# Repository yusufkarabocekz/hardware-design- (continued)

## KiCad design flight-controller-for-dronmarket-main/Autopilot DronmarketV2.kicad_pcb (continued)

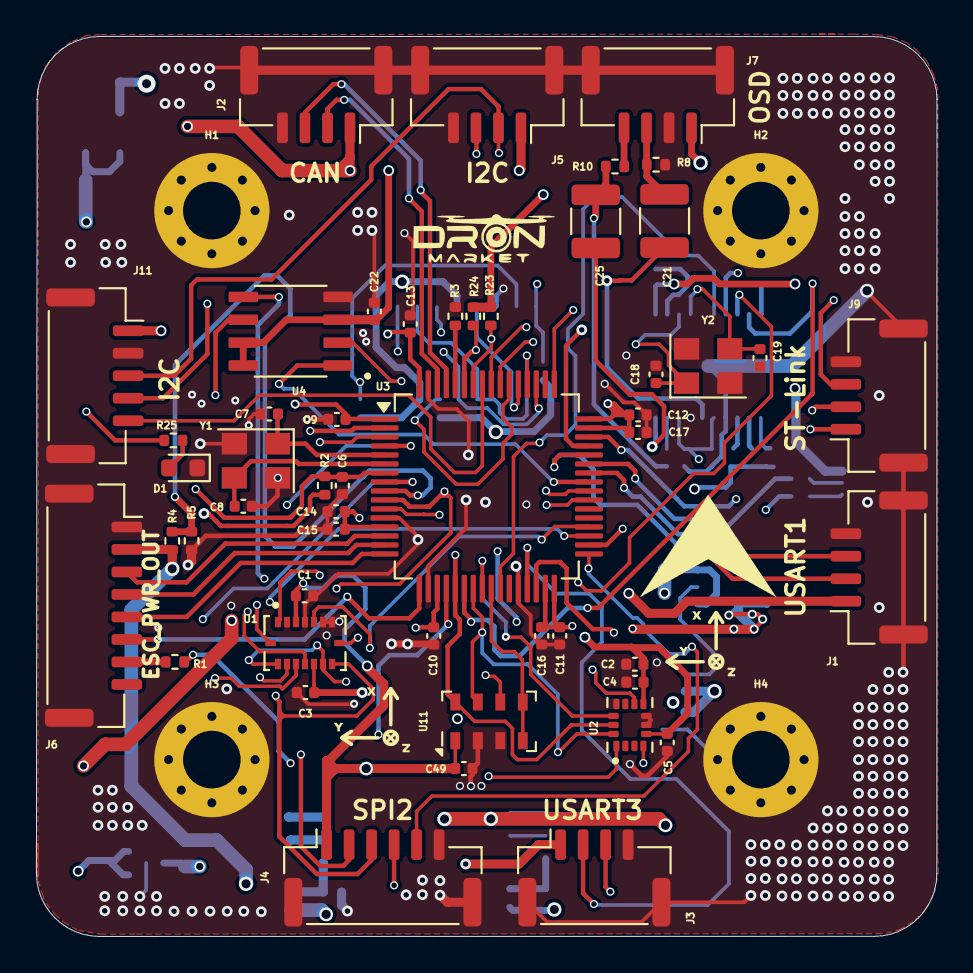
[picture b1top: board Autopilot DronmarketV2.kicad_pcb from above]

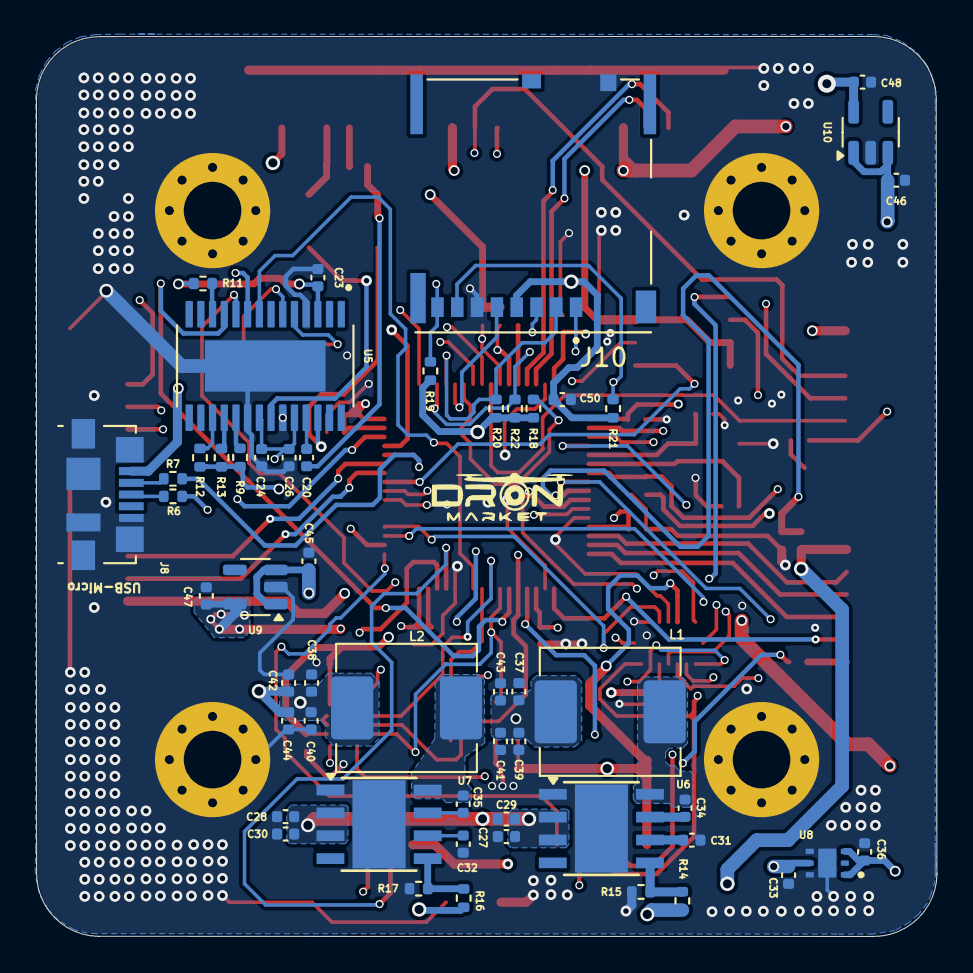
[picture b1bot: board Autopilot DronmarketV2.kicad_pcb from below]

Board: 6 copper layers, 50.0 x 50.0 mm, 111 parts (53 on the bottom side), 79 nets.

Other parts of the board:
., .#2, .#3, .#4, .#5: LOGO
C37, C39: 22uF; C_0402_1005Metric

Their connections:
GND: C37.1, C39.1; also elsewhere on the board
VDD_5V_IN: C37.2, C39.2; also elsewhere on the board

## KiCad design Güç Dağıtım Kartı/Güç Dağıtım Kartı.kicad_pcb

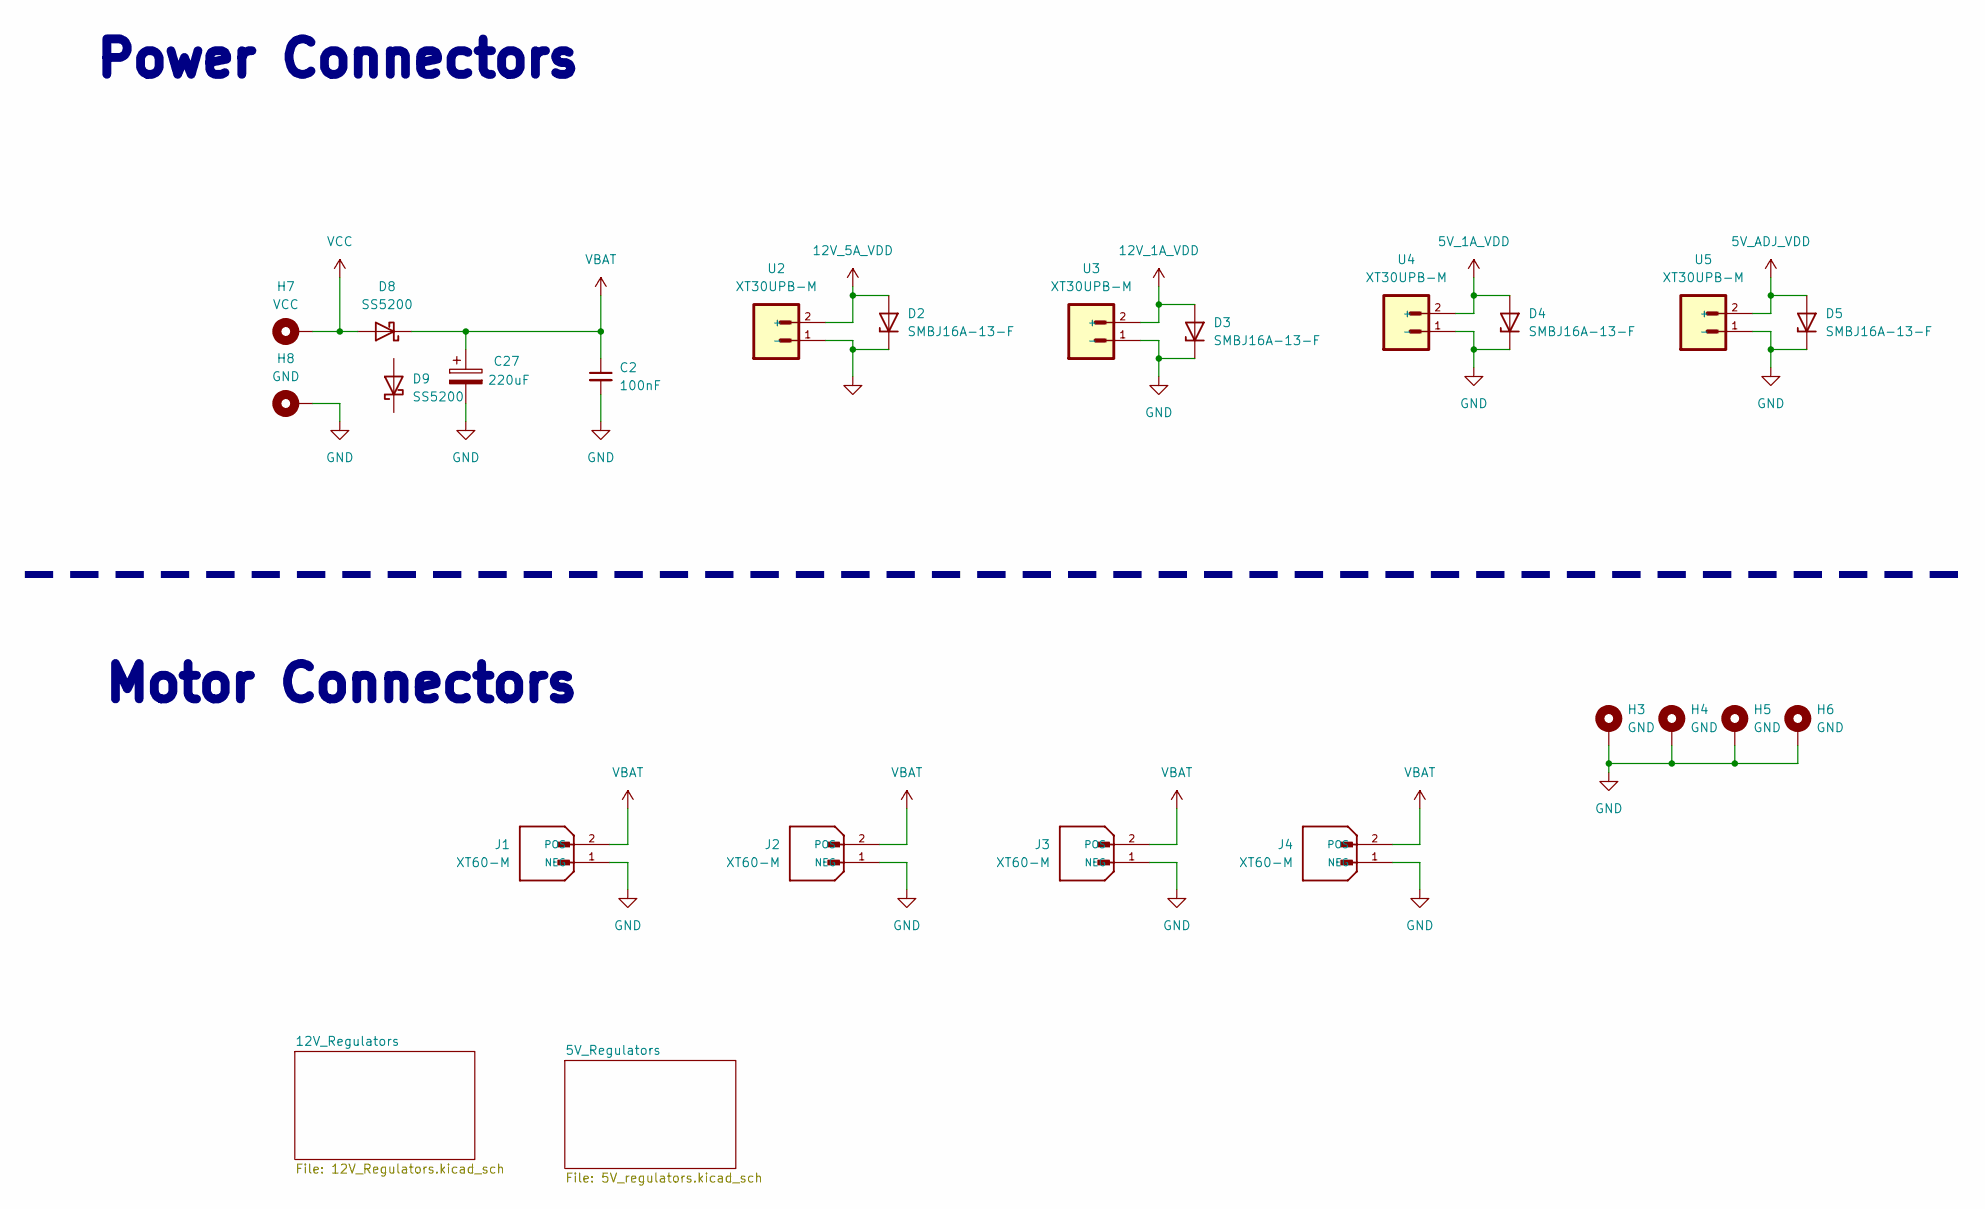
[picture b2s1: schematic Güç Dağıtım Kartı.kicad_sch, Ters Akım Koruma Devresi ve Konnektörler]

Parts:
C2: 100nF; C_1206_3216Metric
C27: 220uF; CP_EIA-7343-43_Kemet-X_HandSolder
D2, D3, D4, D5: SMBJ16A-13-F; D_SMA
D8, D9: SS5200; D_SMA
H3, H4, H5, H6: GND; MountingHole_3.2mm_M3_ISO14580
H7: VCC; MountingHole_4.3mm_M4_Pad_TopOnly
H8: GND; MountingHole_4.3mm_M4_Pad_TopOnly
J1, J2, J3, J4: XT60-M; AMASS_XT60-F_1x02_P7.20mm_Vertical; PARTREV V1.2
U2, U3, U4, U5: XT30UPB-M; AMASS_XT30UPB-M_1x02_P5.0mm_Vertical

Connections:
5V_1A_VDD: D4.2 (A), U4.2 (+); also elsewhere on the board
5V_ADJ_VDD: D5.2 (A), U5.2 (+); also elsewhere on the board
12V_1A_VDD: D3.2 (A), U3.2 (+); also elsewhere on the board
12V_5A_VDD: D2.2 (A), U2.2 (+); also elsewhere on the board
GND: C2.2, C27.2, D2.1 (K), D3.1 (K), D4.1 (K), D5.1 (K), H3.MP, H4.MP, H5.MP, H6.MP, H8.1, J1.1 (NEG), J2.1 (NEG), J3.1 (NEG), J4.1 (NEG), U2.1 (-), U3.1 (-), U4.1 (-), U5.1 (-); also elsewhere on the board
VBAT: C2.1, C27.1, D8.1 (K), J1.2 (POS), J2.2 (POS), J3.2 (POS), J4.2 (POS); also elsewhere on the board
VCC: D8.2 (A), H7.1

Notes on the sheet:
Power Connectors
Motor Connectors

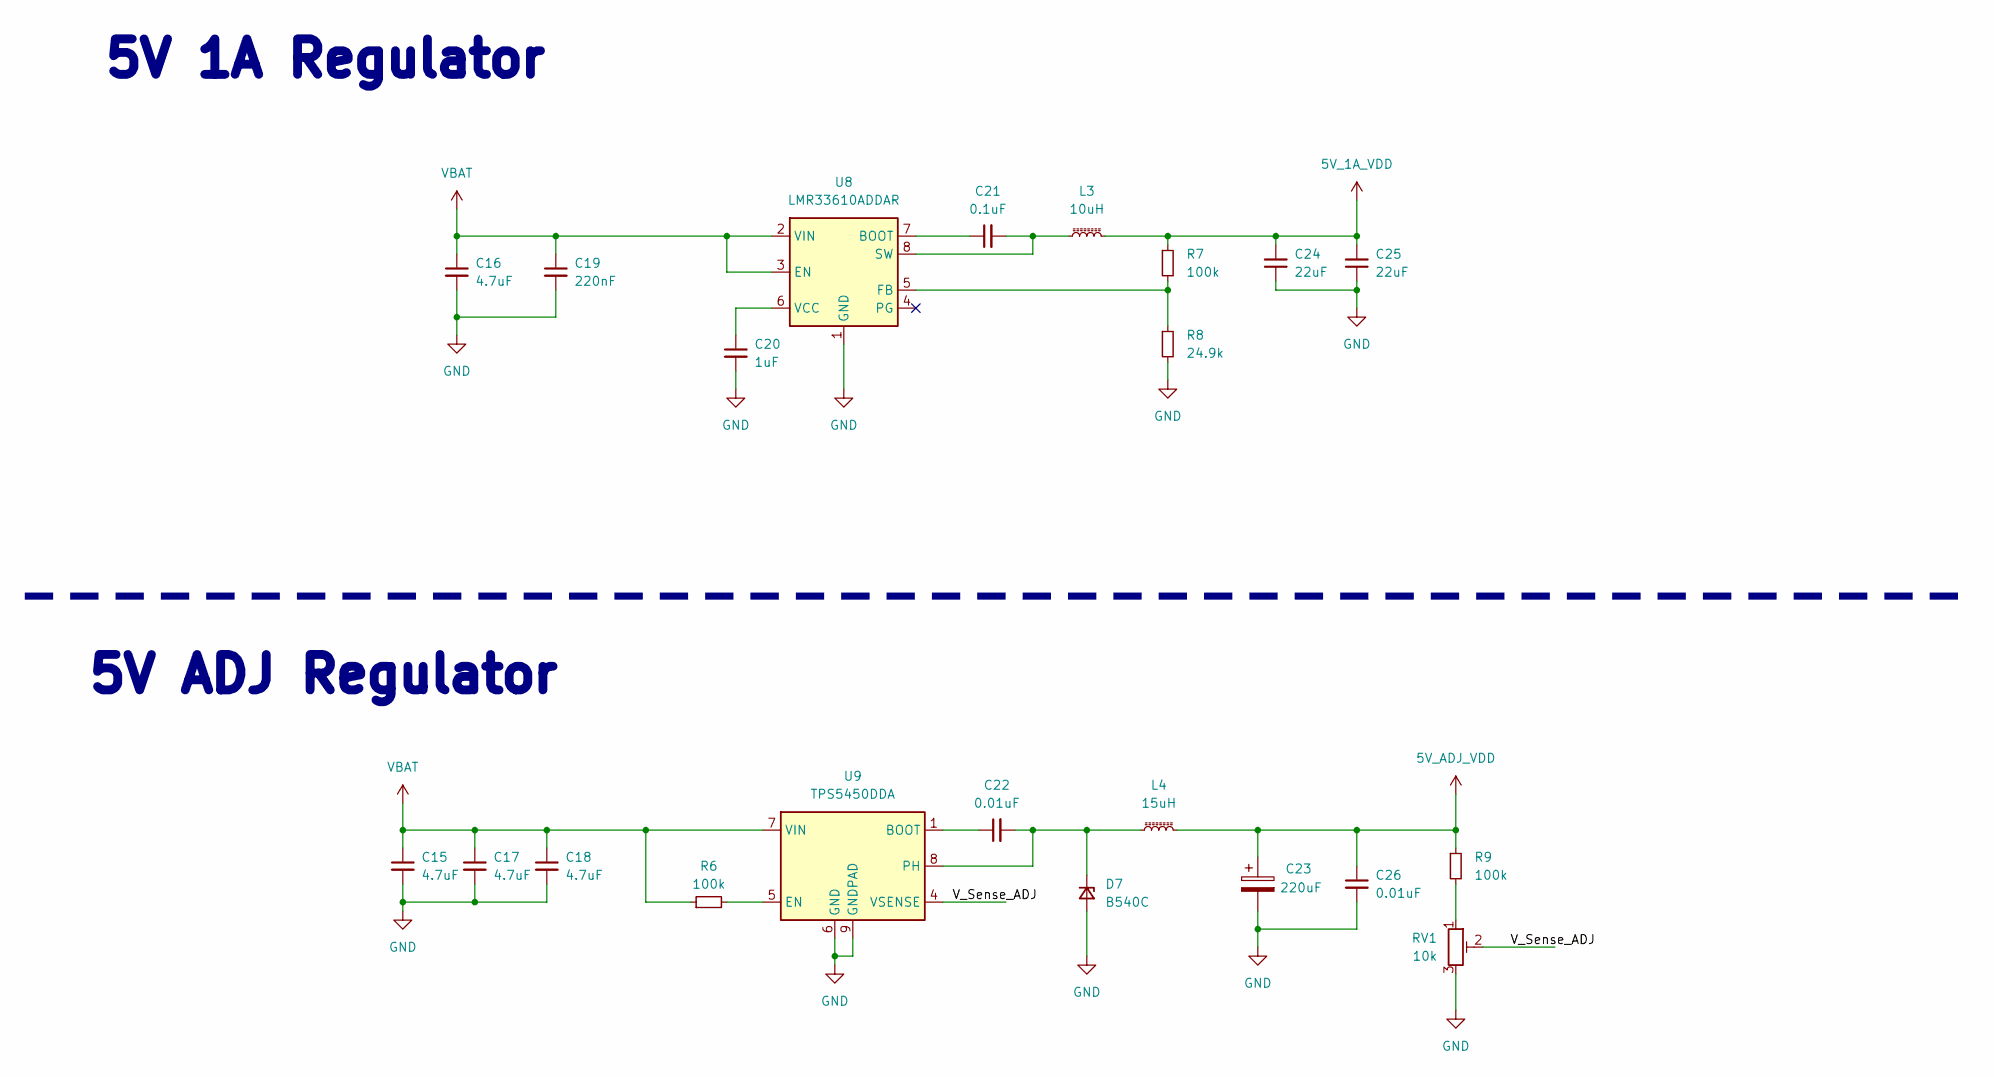
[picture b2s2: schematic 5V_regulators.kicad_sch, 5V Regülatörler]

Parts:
C15, C17, C18: 4.7uF; C_0603_1608Metric_Pad1.08x0.95mm_HandSolder
C16: 4.7uF; C_1206_3216Metric_Pad1.33x1.80mm_HandSolder
C19: 220nF; C_0603_1608Metric_Pad1.08x0.95mm_HandSolder
C20: 1uF; C_0603_1608Metric_Pad1.08x0.95mm_HandSolder
C21: 0.1uF; C_0603_1608Metric_Pad1.08x0.95mm_HandSolder
C22, C26: 0.01uF; C_0603_1608Metric_Pad1.08x0.95mm_HandSolder
C23: 220uF; CP_EIA-7343-43_Kemet-X_HandSolder
C24, C25: 22uF; C_1206_3216Metric_Pad1.33x1.80mm_HandSolder
D7: B540C; D_SMA
L3: 10uH; L_7.3x7.3_H3.5
L4: 15uH; L_7.3x7.3_H3.5
R6, R7, R9: 100k; R_0603_1608Metric_Pad0.98x0.95mm_HandSolder
R8: 24.9k; R_0603_1608Metric_Pad0.98x0.95mm_HandSolder
RV1: 10k; Potentiometer_Bourns_3296W_Vertical
U8: LMR33610ADDAR; Texas_HSOP-8-1EP_3.9x4.9mm_P1.27mm_ThermalVias
U9: TPS5450DDA; TI_SO-PowerPAD-8_ThermalVias

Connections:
5V_1A_VDD: C24.2, C25.2, L3.2, R7.1; also elsewhere on the board
5V_ADJ_VDD: C23.1, C26.1, L4.2, R9.1; also elsewhere on the board
/5V_Regulators/V_Sense_ADJ: RV1.2, U9.4 (VSENSE)
GND: C15.2, C16.2, C17.2, C18.2, C19.2, C20.2, C23.2, C24.1, C25.1, C26.2, D7.2 (A), R8.2, RV1.3, U8.1 (GND), U8.9 (GND), U9.6 (GND), U9.9 (GNDPAD); also elsewhere on the board
unnamed: C22.2, D7.1 (K), L4.1, U9.8 (PH)
unnamed: R9.2, RV1.1
unnamed: C21.1, U8.7 (BOOT)
unnamed: R7.2, R8.1, U8.5 (FB)
unnamed: C21.2, L3.1, U8.8 (SW)
unnamed: C20.1, U8.6 (VCC)
unnamed: C22.1, U9.1 (BOOT)
unnamed: R6.2, U9.5 (EN)
VBAT: C15.1, C16.1, C17.1, C18.1, C19.1, R6.1, U8.2 (VIN), U8.3 (EN), U9.7 (VIN); also elsewhere on the board

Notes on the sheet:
5V ADJ Regulator
5V 1A Regulator

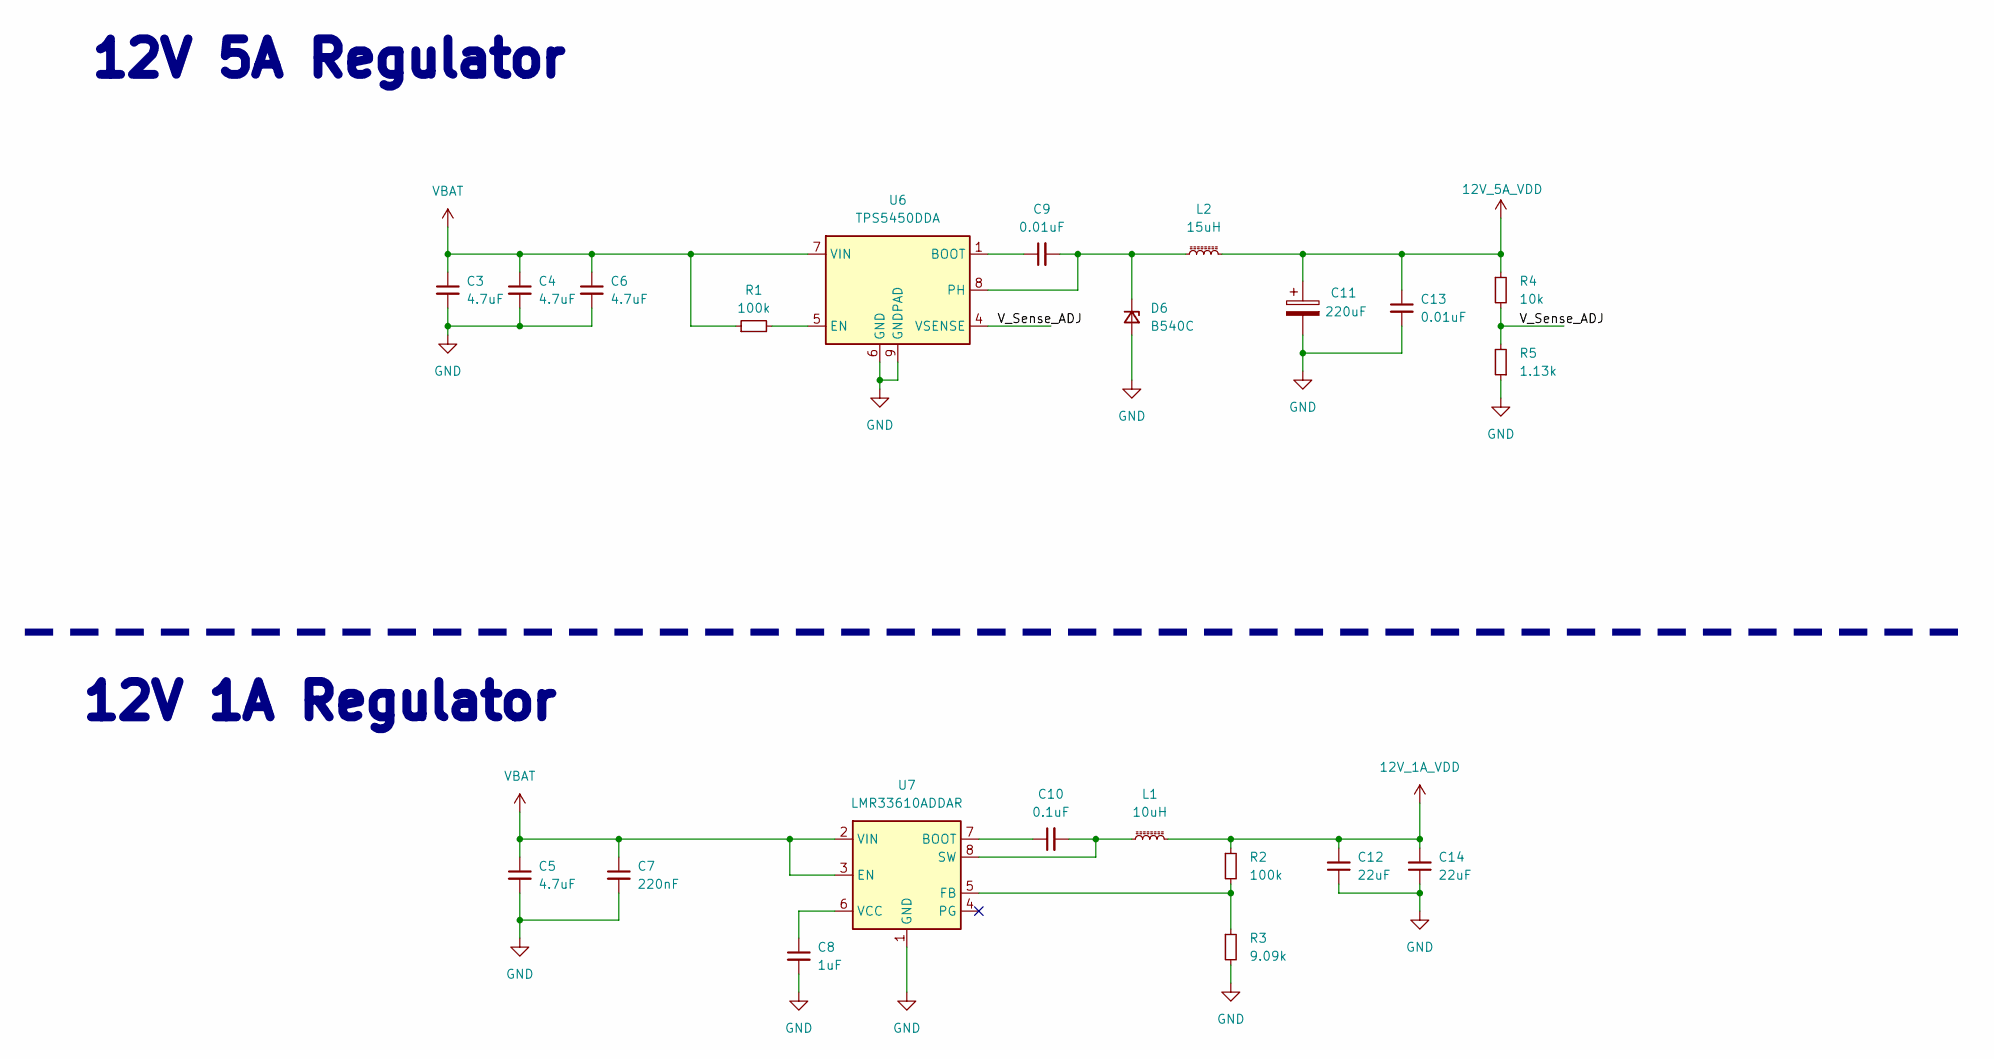
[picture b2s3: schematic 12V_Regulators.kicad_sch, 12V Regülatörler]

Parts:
C3, C4, C6: 4.7uF; C_0603_1608Metric_Pad1.08x0.95mm_HandSolder
C5: 4.7uF; C_1206_3216Metric_Pad1.33x1.80mm_HandSolder
C7: 220nF; C_0603_1608Metric_Pad1.08x0.95mm_HandSolder
C8: 1uF; C_0603_1608Metric_Pad1.08x0.95mm_HandSolder
C9, C13: 0.01uF; C_0603_1608Metric_Pad1.08x0.95mm_HandSolder
C10: 0.1uF; C_0603_1608Metric_Pad1.08x0.95mm_HandSolder
C11: 220uF; CP_EIA-7343-43_Kemet-X_HandSolder
C12, C14: 22uF; C_1206_3216Metric_Pad1.33x1.80mm_HandSolder
D6: B540C; D_SMA
L1: 10uH; L_7.3x7.3_H3.5
L2: 15uH; L_7.3x7.3_H3.5
R1, R2: 100k; R_0603_1608Metric_Pad0.98x0.95mm_HandSolder
R3: 9.09k; R_0603_1608Metric_Pad0.98x0.95mm_HandSolder
R4: 10k; R_0603_1608Metric_Pad0.98x0.95mm_HandSolder
R5: 1.13k; R_0603_1608Metric_Pad0.98x0.95mm_HandSolder
U6: TPS5450DDA; TI_SO-PowerPAD-8_ThermalVias
U7: LMR33610ADDAR; Texas_HSOP-8-1EP_3.9x4.9mm_P1.27mm_ThermalVias

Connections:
12V_1A_VDD: C12.2, C14.2, L1.2, R2.1; also elsewhere on the board
12V_5A_VDD: C11.1, C13.1, L2.2, R4.1; also elsewhere on the board
/12V_Regulators/V_Sense_ADJ: R4.2, R5.2, U6.4 (VSENSE)
GND: C3.2, C4.2, C5.2, C6.2, C7.2, C8.2, C11.2, C12.1, C13.2, C14.1, D6.2 (A), R3.2, R5.1, U6.6 (GND), U6.9 (GNDPAD), U7.1 (GND), U7.9 (GND); also elsewhere on the board
unnamed: C9.2, D6.1 (K), L2.1, U6.8 (PH)
unnamed: C9.1, U6.1 (BOOT)
unnamed: R1.2, U6.5 (EN)
unnamed: C10.1, U7.7 (BOOT)
unnamed: R2.2, R3.1, U7.5 (FB)
unnamed: C10.2, L1.1, U7.8 (SW)
unnamed: C8.1, U7.6 (VCC)
VBAT: C3.1, C4.1, C5.1, C6.1, C7.1, R1.1, U6.7 (VIN), U7.2 (VIN), U7.3 (EN); also elsewhere on the board

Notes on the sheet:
12V 5A Regulator
12V 1A Regulator

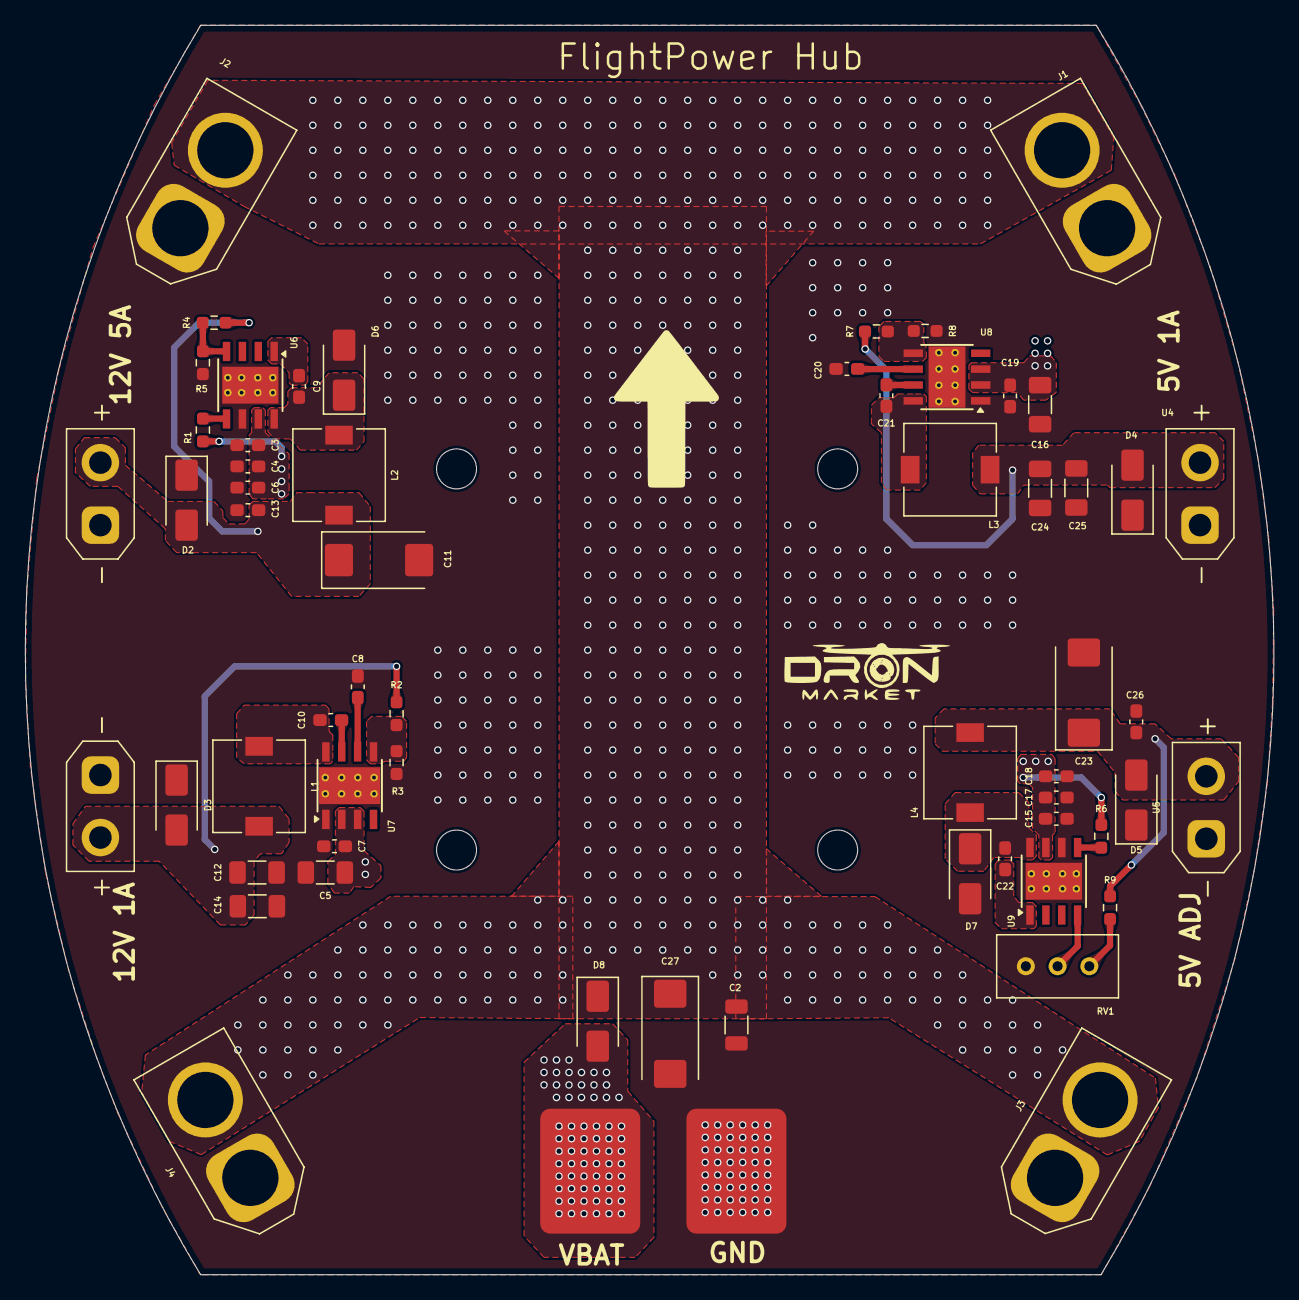
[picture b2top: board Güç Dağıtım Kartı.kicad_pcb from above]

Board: 4 copper layers, 99.9 x 100.0 mm, 65 parts (0 on the bottom side), 24 nets.

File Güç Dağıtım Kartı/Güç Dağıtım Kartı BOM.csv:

Id;Designator;Footprint;Quantity;Designation;Supplier and ref
1;J3,M1,J1,J4;AMASS_XT60-F_1x02_P7.20mm_Vertical;4;XT60-M;
2;,,,,,,,,,,,,,,,,,,,,,,,,,,,,,,,,,,,,;;37;;
3;R2,R7,R6,R9,R1;R_0603_1608Metric;5;100k;
4;D6,D7;D_SMA;2;B540C;
5;C26,C22,C9,C13;C_0603_1608Metric_Pad1.08x0.95mm_HandSolder;4;0.01uF;
6;12V_5A Jetson Nano,12V_1A;AMASS_XT30UPB-M_1x02_P5.0mm_Vertical;2;XT30UPB-M;
7;R4;R_0603_1608Metric;1;10k;
8;C8,C20;C_0603_1608Metric_Pad1.08x0.95mm_HandSolder;2;1uF;
9;C16,C5;C_1206_3216Metric;2;4.7uF;
10;C19,C7;C_0603_1608Metric_Pad1.08x0.95mm_HandSolder;2;220nF;
11;RV1;Potentiometer_Bourns_3266Z_Horizontal;1;10k;
12;C3,C6,C18,C4,C15,C17;C_0603_1608Metric_Pad1.08x0.95mm_HandSolder;6;4.7uF;
13;R5;R_0603_1608Metric;1;1.13k;
14;R8;R_0603_1608Metric;1;24.9k;
15;L4,L2;L_Wurth_WE-LQSH-4020;2;15uH;
16;U6,U9;TI_SO-PowerPAD-8_ThermalVias;2;TPS5450DDA;
17;D4,D2,D5,D3;D_SMA;4;D_Zener;
18;5V_1A,5V_ADJ;AMASS_XT30U-F_1x02_P5.0mm_Vertical;2;XT30UPB-M;
19;C12,C14,C25,C24;C_1206_3216Metric;4;22uF;
20;U8,U7;Texas_HSOP-8-1EP_3.9x4.9mm_P1.27mm_ThermalVias;2;LMR33610ADDAR;
21;C11,C23;CP_EIA-1608-10_AVX-L;2;330uF;
22;;29548ad2-03e3-42cf-bff7-278db09b4abb;1;;
23;D1;D_SMA_Handsoldering;1;SB130;
24;L3,L1;L_Wurth_WE-LQSH-4020;2;10uH;
25;C1;CP_EIA-7343-40_Kemet-Y;1;C_Polarized;
26;C2;C_1206_3216Metric;1;100nF;
27;R3;R_0603_1608Metric;1;9.09k;
28;C21,C10;C_0603_1608Metric_Pad1.08x0.95mm_HandSolder;2;0.1uF;
29;;2d8a1ed6-01ba-462d-b9ff-4f236c5c597e;1;;

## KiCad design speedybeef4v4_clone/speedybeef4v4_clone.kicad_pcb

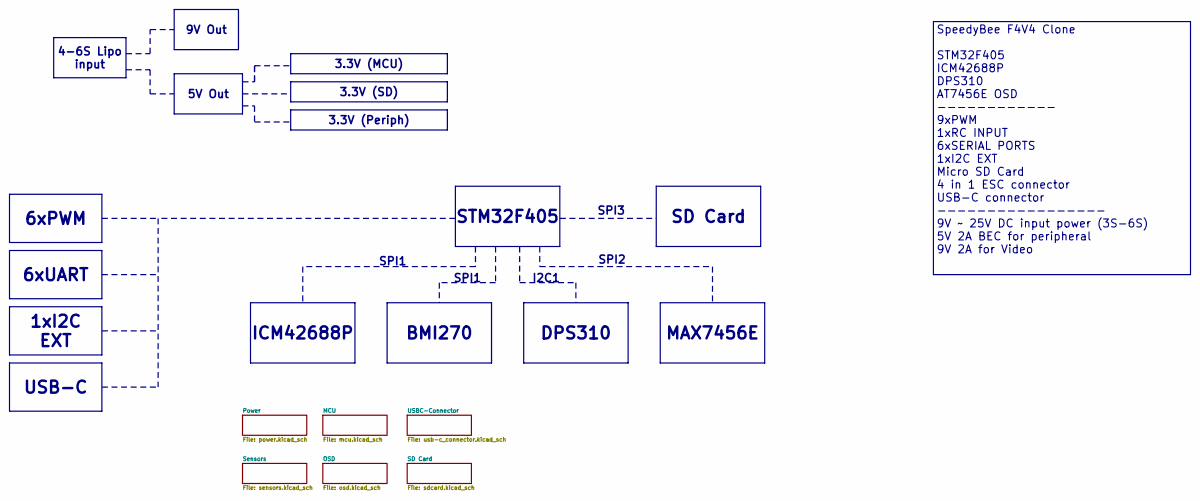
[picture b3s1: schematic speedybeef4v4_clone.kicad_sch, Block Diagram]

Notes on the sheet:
SPI3
I2C1
SPI1
SPI2
DPS310
5V Out
1xI2C EXT
SD Card
6xPWM
9V Out
MAX7456E
3.3V (MCU)
3.3V (Periph)
SpeedyBee F4V4 Clone STM32F405 ICM42688P DPS310 AT7456E OSD ------------ 9xPWM 1xRC INPUT 6xSERIAL PORTS 1xI2C EXT Micro SD Card 4 in 1 ESC connector USB-C connector ----------------- 9V ~ 25V DC input power (3S-6S) 5V 2A BEC for peripheral 9V 2A for Video
6xUART
USB-C
STM32F405
4-6S Lipo input
BMI270
ICM42688P
3.3V (SD)

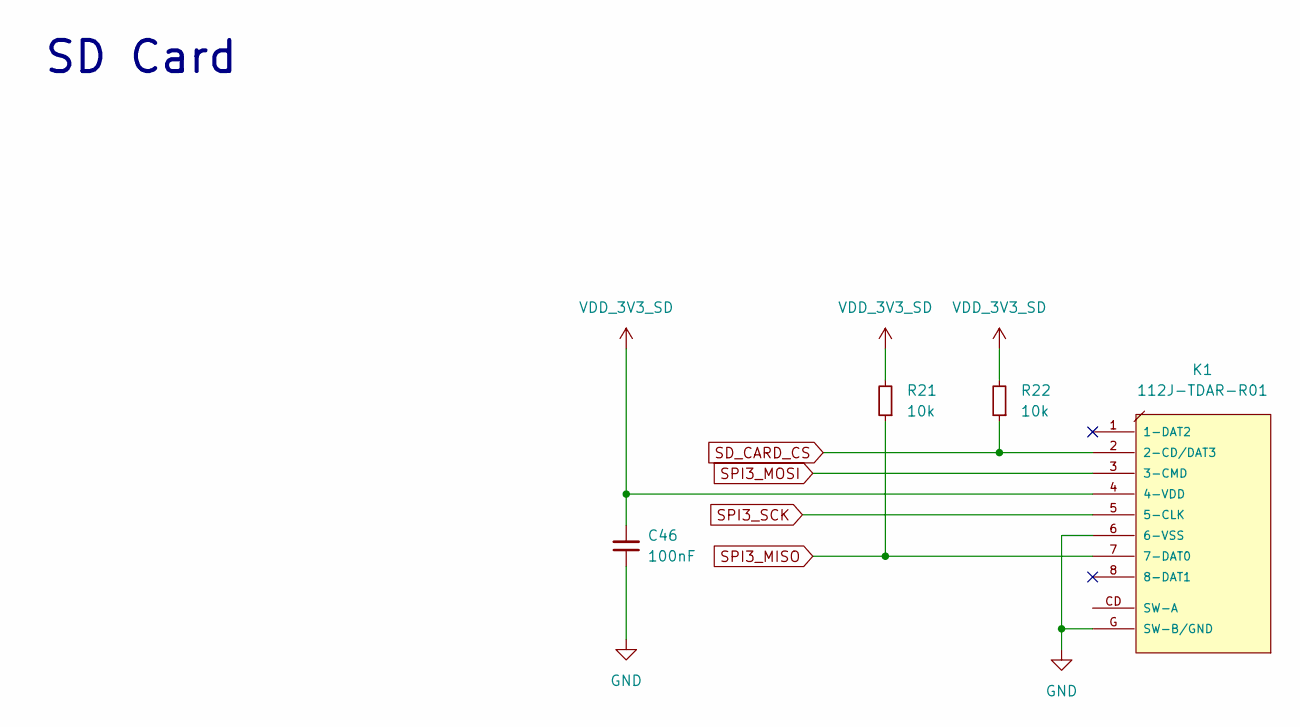
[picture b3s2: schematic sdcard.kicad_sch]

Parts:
C46: 100nF; C_0402_1005Metric
K1: 112J-TDAR-R01
R21, R22: 10k; R_0402_1005Metric

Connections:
GND: C46.1, K1.6 (6-VSS), K1.G (SW-B/GND); also elsewhere on the board
SD_CARD_CS: K1.2 (2-CD/DAT3), R22.1; also elsewhere on the board
SPI3_MISO: K1.7 (7-DAT0), R21.1; also elsewhere on the board
SPI3_MOSI: K1.3 (3-CMD); also elsewhere on the board
SPI3_SCK: K1.5 (5-CLK); also elsewhere on the board
VDD_3V3_SD: C46.2, K1.4 (4-VDD), R21.2, R22.2; also elsewhere on the board

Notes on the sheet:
SD Card

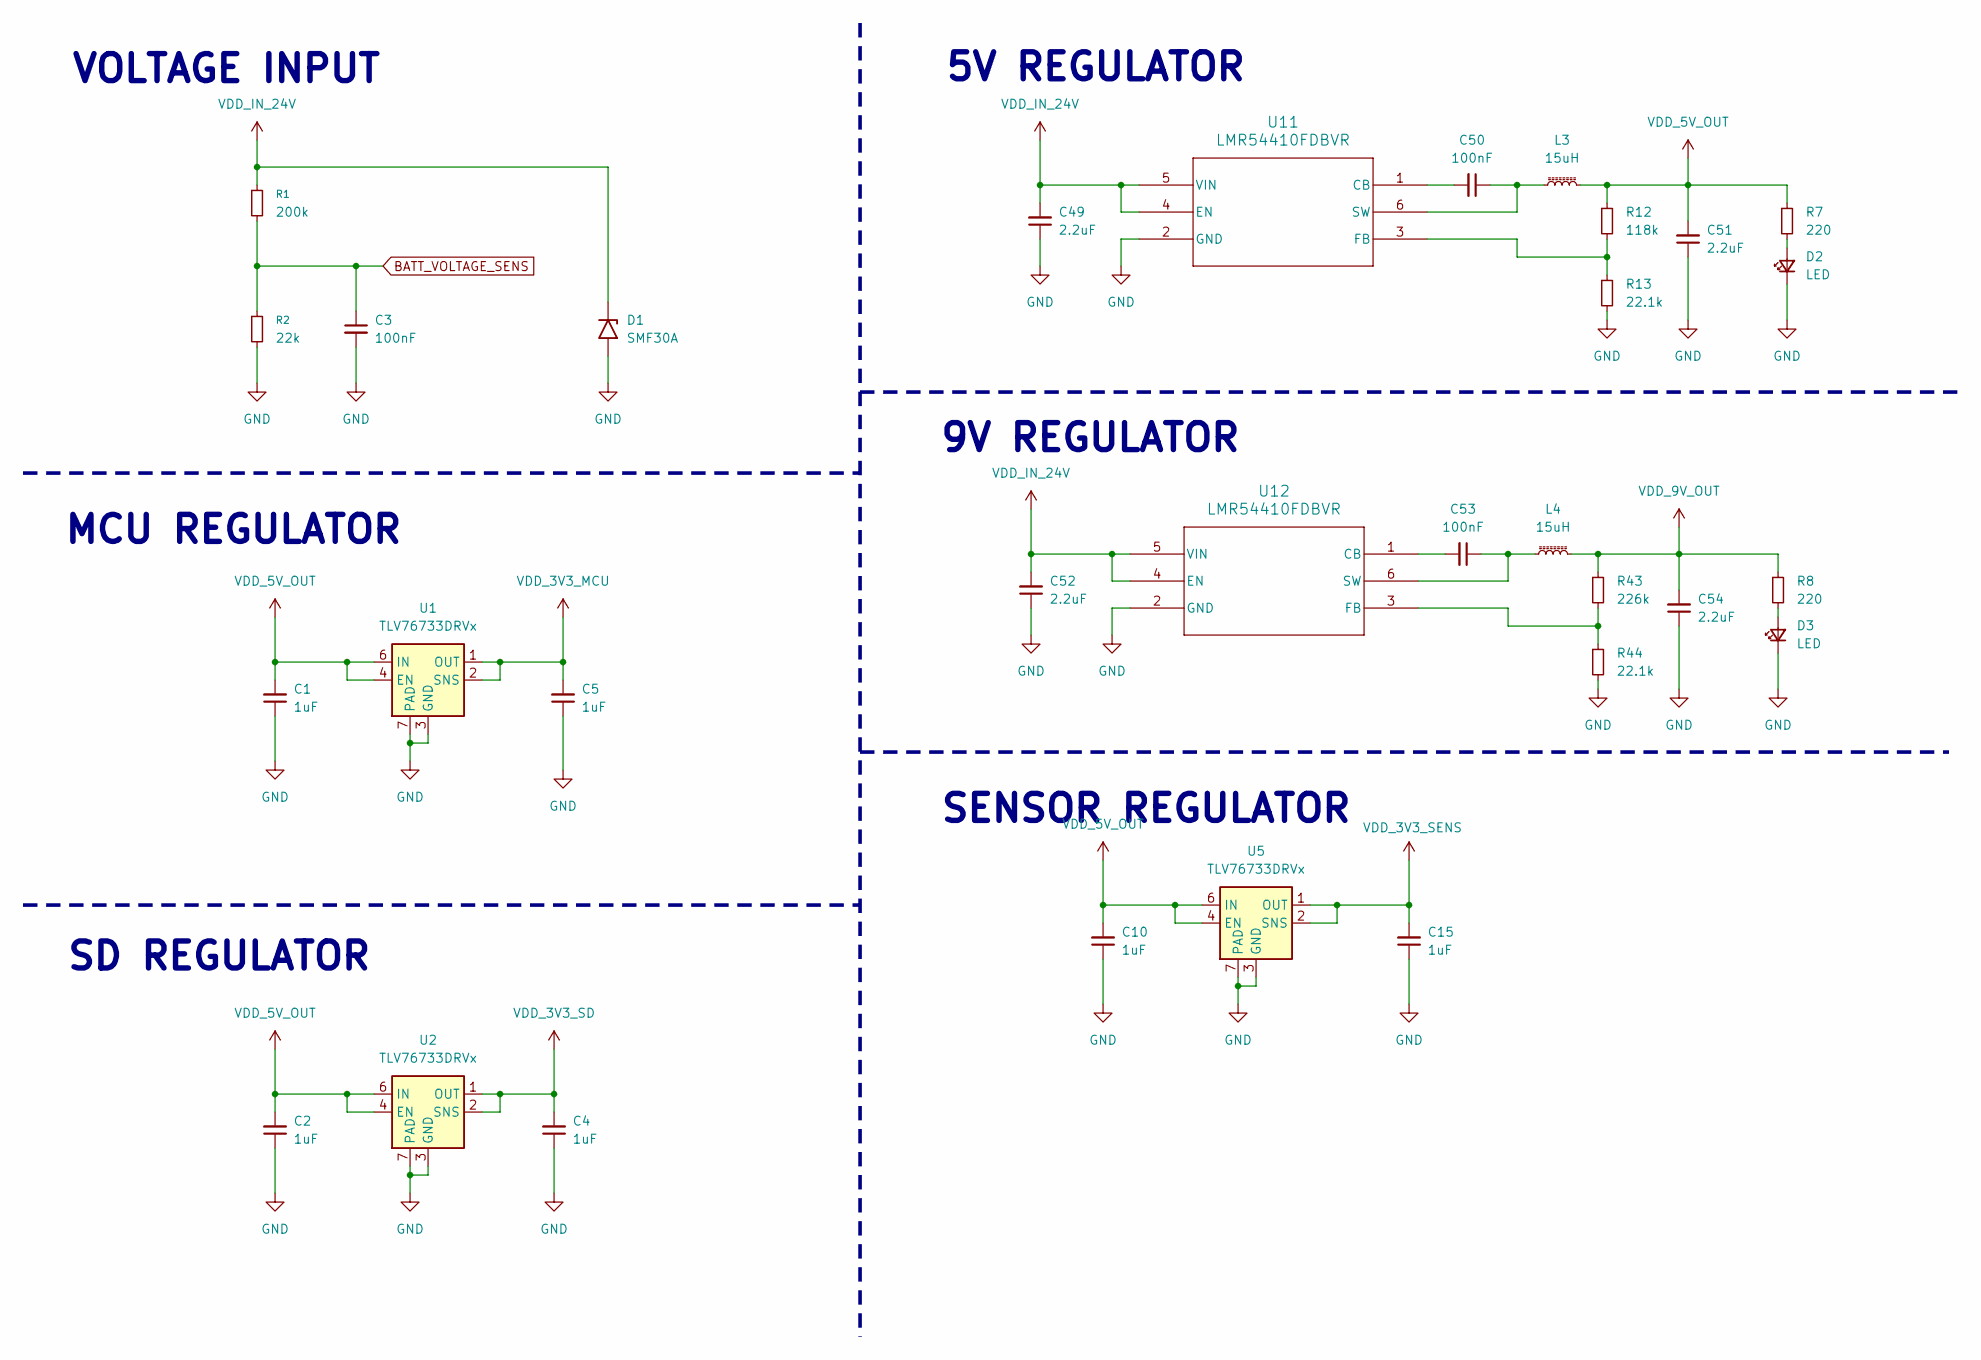
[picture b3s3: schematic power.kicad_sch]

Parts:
C1, C2, C4, C5, C10, C15: 1uF; C_0603_1608Metric
C3, C50, C53: 100nF; C_0402_1005Metric
C49, C51, C52, C54: 2.2uF; C_0603_1608Metric
D1: SMF30A; D_SMF
D2, D3: LED; LED_0402_1005Metric
L3, L4: 15uH; L_Sunlord_MWSA0402S
R1: 200k; R_0603_1608Metric
R2: 22k; R_0603_1608Metric
R7, R8: 220; R_0402_1005Metric
R12: 118k; R_0402_1005Metric
R13, R44: 22.1k; R_0402_1005Metric
R43: 226k; R_0402_1005Metric
U1, U2, U5: TLV76733DRVx; WSON-6-1EP_2x2mm_P0.65mm_EP1x1.6mm_ThermalVias
U11, U12: LMR54410FDBVR; SOT-23-6-DBV_TEX-L

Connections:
BATT_VOLTAGE_SENS: C3.1, R1.2, R2.1; also elsewhere on the board
GND: C1.1, C2.1, C3.2, C4.1, C5.1, C10.1, C15.1, C49.1, C51.1, C52.1, C54.1, D1.2 (A2), D2.1 (K), D3.1 (K), R2.2, R13.2, R44.2, U1.3 (GND), U1.5 (GND), U1.7 (PAD), U2.3 (GND), U2.5 (GND), U2.7 (PAD), U5.3 (GND), U5.5 (GND), U5.7 (PAD), U11.2 (GND), U12.2 (GND); also elsewhere on the board
unnamed: D2.2 (A), R7.2
unnamed: D3.2 (A), R8.2
unnamed: C50.2, U11.1 (CB)
unnamed: R12.2, R13.1, U11.3 (FB)
unnamed: C50.1, L3.1, U11.6 (SW)
unnamed: C53.2, U12.1 (CB)
unnamed: R43.2, R44.1, U12.3 (FB)
unnamed: C53.1, L4.1, U12.6 (SW)
VDD_3V3_MCU: C5.2, U1.1 (OUT), U1.2 (SNS); also elsewhere on the board
VDD_3V3_SD: C4.2, U2.1 (OUT), U2.2 (SNS); also elsewhere on the board
VDD_3V3_SENS: C15.2, U5.1 (OUT), U5.2 (SNS); also elsewhere on the board
VDD_5V_OUT: C1.2, C2.2, C10.2, C51.2, L3.2, R7.1, R12.1, U1.4 (EN), U1.6 (IN), U2.4 (EN), U2.6 (IN), U5.4 (EN), U5.6 (IN); also elsewhere on the board
VDD_9V_OUT: C54.2, L4.2, R8.1, R43.1
VDD_IN_24V: C49.2, C52.2, D1.1 (A1), R1.1, U11.4 (EN), U11.5 (VIN), U12.4 (EN), U12.5 (VIN); also elsewhere on the board

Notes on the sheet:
SENSOR REGULATOR
5V REGULATOR
9V REGULATOR
VOLTAGE INPUT
MCU REGULATOR
SD REGULATOR
